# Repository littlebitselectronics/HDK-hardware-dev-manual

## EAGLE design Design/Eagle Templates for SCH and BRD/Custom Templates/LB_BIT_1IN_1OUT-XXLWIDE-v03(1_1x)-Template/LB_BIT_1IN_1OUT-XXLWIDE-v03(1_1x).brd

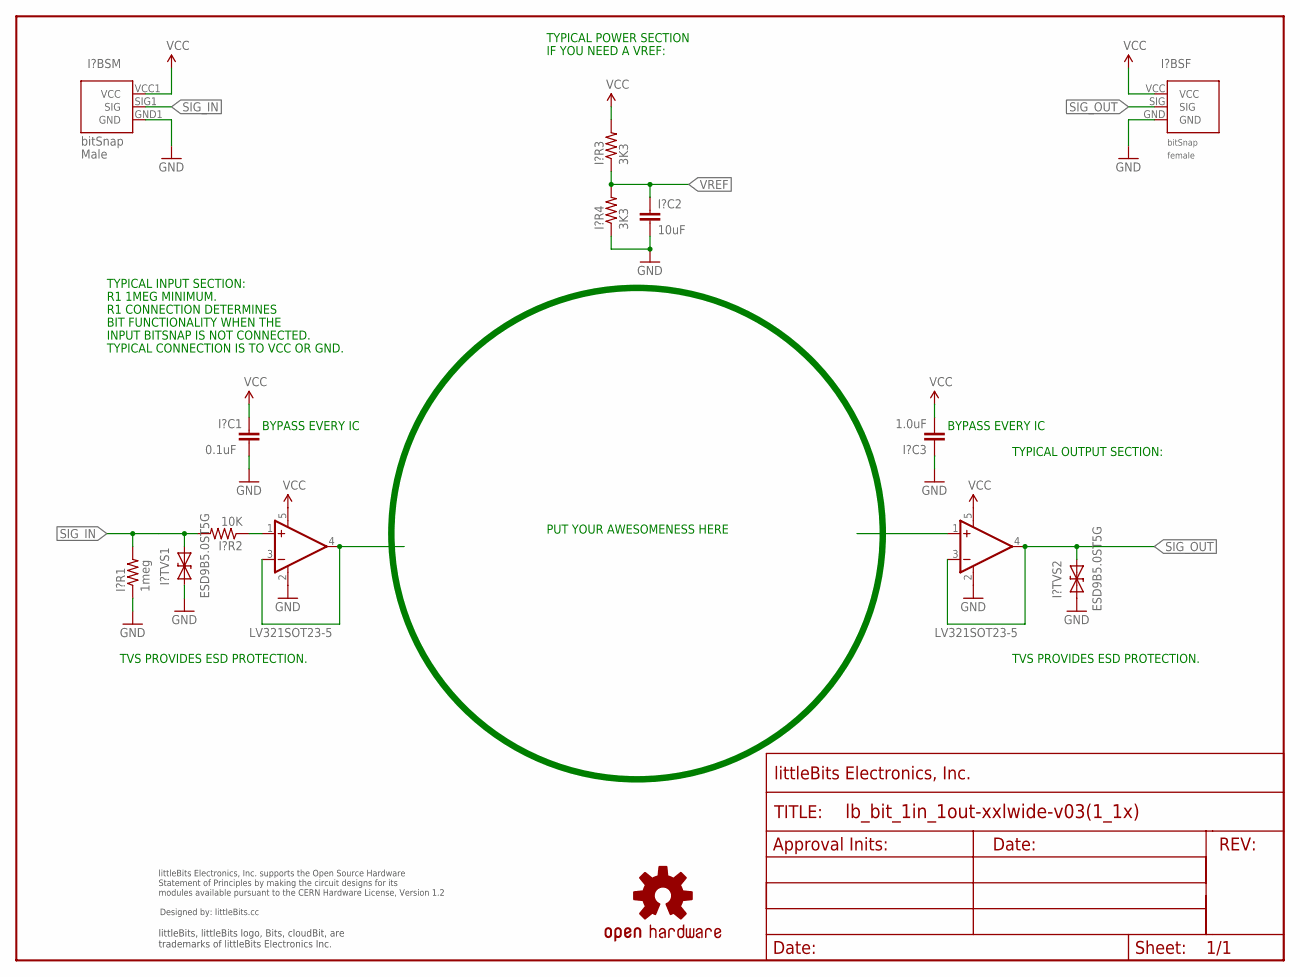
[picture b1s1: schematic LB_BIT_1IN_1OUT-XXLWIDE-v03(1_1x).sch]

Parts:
FRAME1: FRAME-LETTER; FABDWG01-OHW
I?BSF: BITSNAP_V03_FEMALE
I?BSM: BITSNAP_V03_MALE
I?C1: 0.1uF; CAP-0603
I?C2: 10uF; CAP-0603
I?C3: 1.0uF; CAP-0603
I?R1: 1meg; RES-0603
I?R2: 10K; RES-0603
I?R3, I?R4: 3K3; RES-0603
I?TVS1, I?TVS2: ESD9B5.0ST5G; SOD-923
U1, U2: LV321SOT23-5; SOT23-5
U$1: OSHWCREDIT
U$2: OSHW-LOGOL; OSHW-LOGO-L

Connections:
GND: I?BSF.GND, I?BSM.GND1 (GND), I?C1.2, I?C2.2, I?C3.1, I?R1.1, I?R4.1, I?TVS1.1 (A), I?TVS2.1 (A), U1.2 (V-), U2.2 (V-)
unnamed: U1.3 (-IN), U1.4 (OUT)
unnamed: I?R2.1, U1.1 (+IN)
SIG_IN: I?BSM.SIG1 (SIG), I?R1.2, I?R2.2, I?TVS1.2 (C)
SIG_OUT: I?BSF.SIG, I?TVS2.2 (C), U2.3 (-IN), U2.4 (OUT)
VCC: I?BSF.VCC, I?BSM.VCC1 (VCC), I?C1.1, I?C3.2, I?R3.2, U1.5 (V+), U2.5 (V+)
VREF: I?C2.1, I?R3.1, I?R4.2

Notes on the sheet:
R1 1MEG MINIMUM.
R1 CONNECTION DETERMINES
BIT FUNCTIONALITY WHEN THE
INPUT BITSNAP IS NOT CONNECTED.
TYPICAL CONNECTION IS TO VCC OR GND.
TVS PROVIDES ESD PROTECTION.
TYPICAL INPUT SECTION:
TYPICAL OUTPUT SECTION:
PUT YOUR AWESOMENESS HERE
BYPASS EVERY IC
TYPICAL POWER SECTION
IF YOU NEED A VREF:

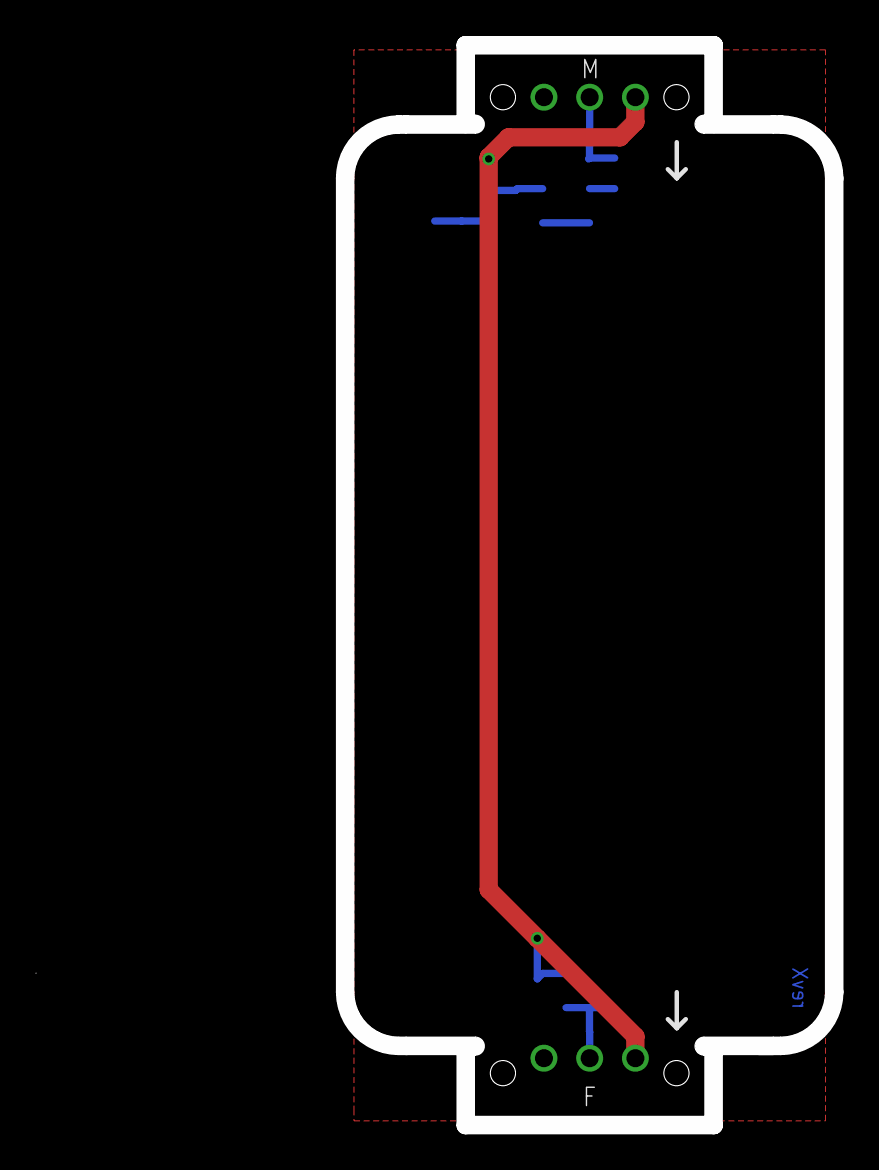
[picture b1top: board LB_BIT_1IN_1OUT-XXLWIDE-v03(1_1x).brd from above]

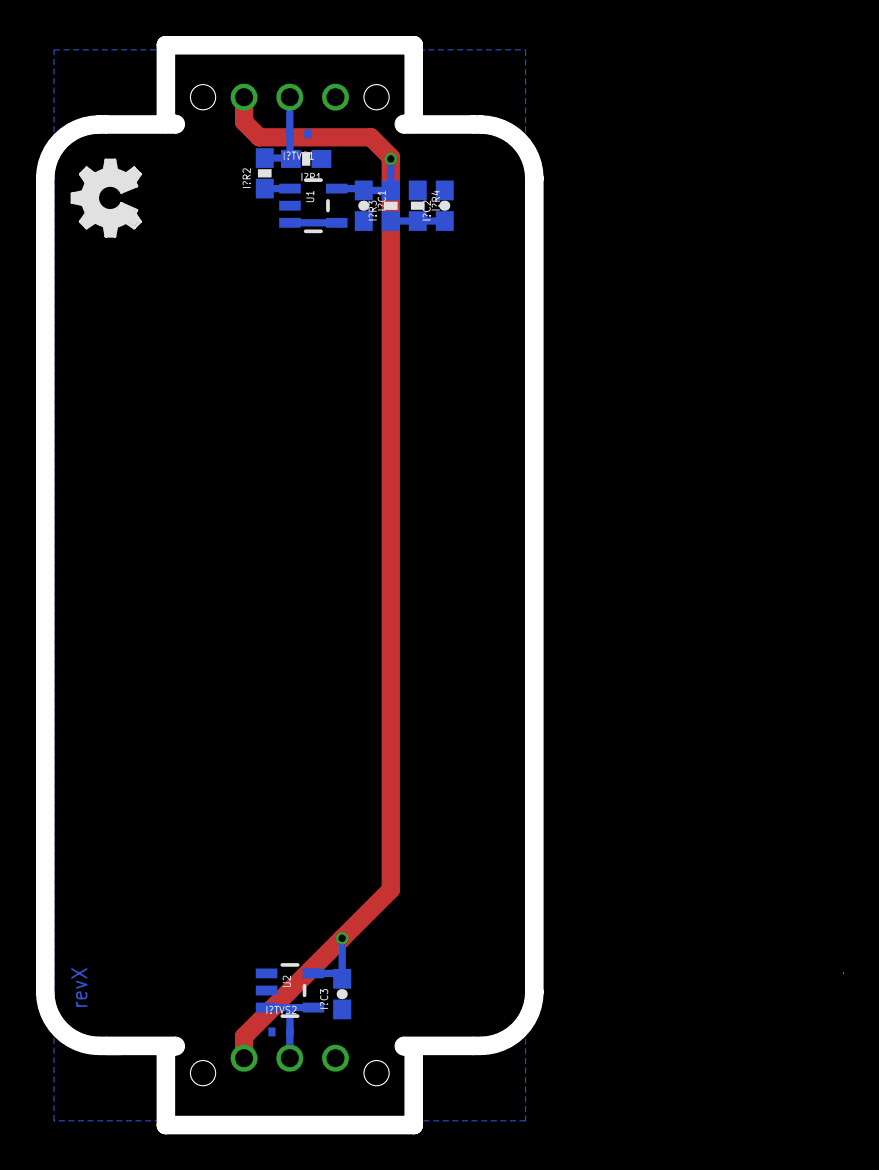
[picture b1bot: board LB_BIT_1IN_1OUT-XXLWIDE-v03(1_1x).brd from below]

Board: 2 copper layers, 26.2 x 59.0 mm, 17 parts (12 on the bottom side), 7 nets.

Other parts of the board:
U$4: OSHW_FILLX150_NOTEXT

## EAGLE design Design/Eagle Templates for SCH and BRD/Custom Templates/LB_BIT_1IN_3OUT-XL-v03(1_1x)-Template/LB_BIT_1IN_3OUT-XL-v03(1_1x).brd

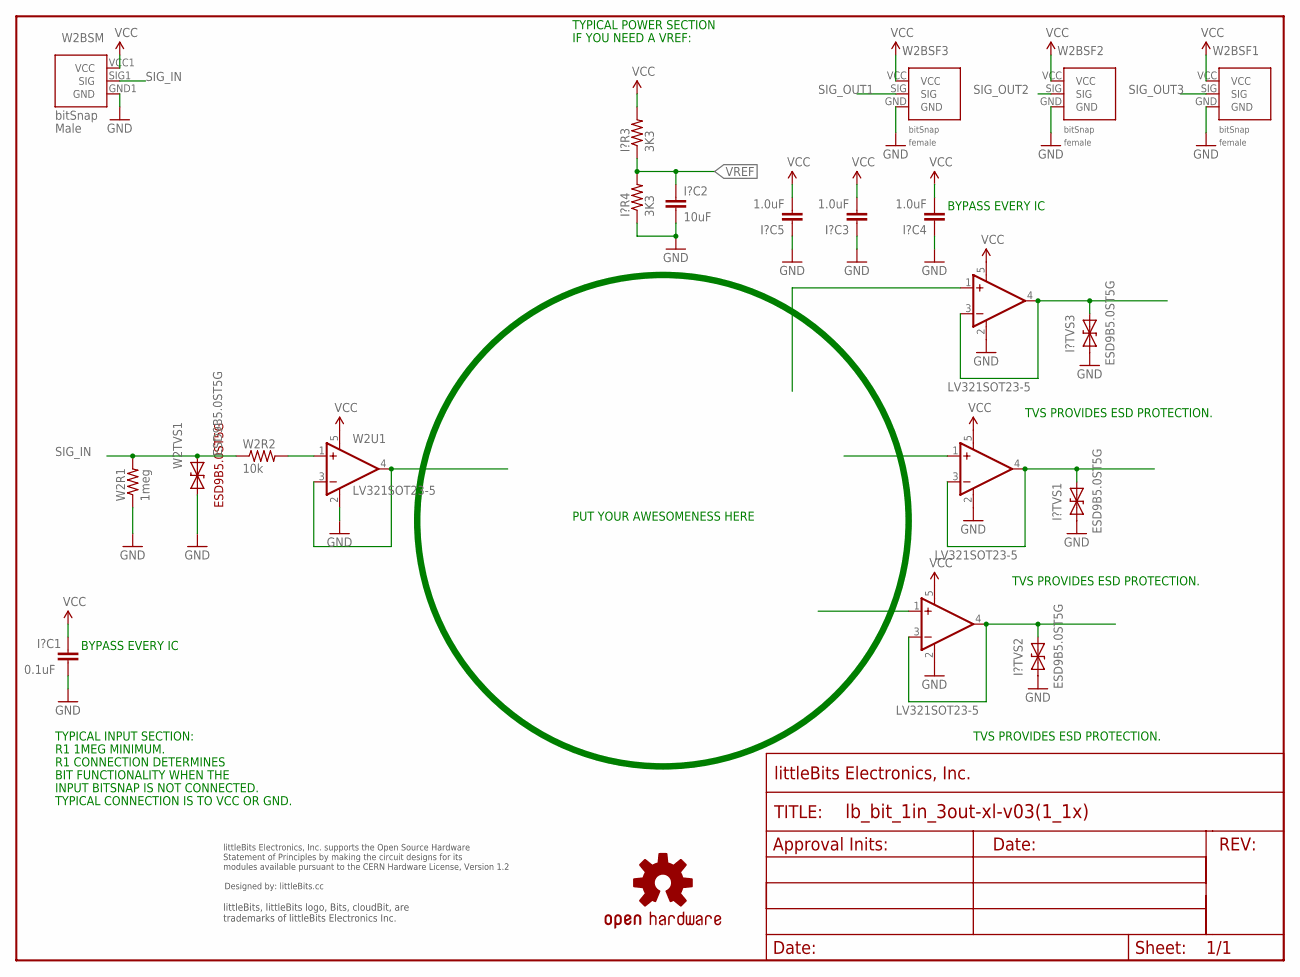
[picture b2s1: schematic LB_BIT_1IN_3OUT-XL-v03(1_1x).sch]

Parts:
FRAME1: FRAME-LETTER; FABDWG01-OHW
I?C1: 0.1uF; CAP-0603
I?C2: 10uF; CAP-0603
I?C3, I?C4, I?C5: 1.0uF; CAP-0603
I?R3, I?R4: 3K3; RES-0603
I?TVS1, I?TVS2, I?TVS3: ESD9B5.0ST5G; SOD-923
U1, U2, U3: LV321SOT23-5; SOT23-5
U$1: OSHWCREDIT
U$6: OSHW-LOGOL; OSHW-LOGO-L
W2BSF1, W2BSF2, W2BSF3: BITSNAP_V03_FEMALE
W2BSM: BITSNAP_V03_MALE
W2R1: 1meg; RES-0603
W2R2: 10k; RES-0603
W2TVS1: ESD9B5.0ST5G; SOD-923
W2U1: LV321SOT23-5; SOT23-5

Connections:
GND: I?C1.2, I?C2.2, I?C3.1, I?C4.1, I?C5.1, I?R4.1, I?TVS1.1 (A), I?TVS2.1 (A), I?TVS3.1 (A), U1.2 (V-), U2.2 (V-), U3.2 (V-), W2BSF1.GND, W2BSF2.GND, W2BSF3.GND, W2BSM.GND1 (GND), W2R1.1, W2TVS1.1 (A), W2U1.2 (V-)
unnamed: W2U1.3 (-IN), W2U1.4 (OUT)
unnamed: W2R2.2, W2U1.1 (+IN)
SIG_IN: W2BSM.SIG1 (SIG), W2R1.2, W2R2.1, W2TVS1.2 (C)
SIG_OUT1: I?TVS3.2 (C), U3.3 (-IN), U3.4 (OUT), W2BSF3.SIG
SIG_OUT2: I?TVS1.2 (C), U1.3 (-IN), U1.4 (OUT), W2BSF2.SIG
SIG_OUT3: I?TVS2.2 (C), U2.3 (-IN), U2.4 (OUT), W2BSF1.SIG
VCC: I?C1.1, I?C3.2, I?C4.2, I?C5.2, I?R3.2, U1.5 (V+), U2.5 (V+), U3.5 (V+), W2BSF1.VCC, W2BSF2.VCC, W2BSF3.VCC, W2BSM.VCC1 (VCC), W2U1.5 (V+)
VREF: I?C2.1, I?R3.1, I?R4.2

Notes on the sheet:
R1 1MEG MINIMUM.
R1 CONNECTION DETERMINES
BIT FUNCTIONALITY WHEN THE
INPUT BITSNAP IS NOT CONNECTED.
TYPICAL CONNECTION IS TO VCC OR GND.
TYPICAL INPUT SECTION:
TYPICAL POWER SECTION
IF YOU NEED A VREF:
TVS PROVIDES ESD PROTECTION.
PUT YOUR AWESOMENESS HERE
BYPASS EVERY IC

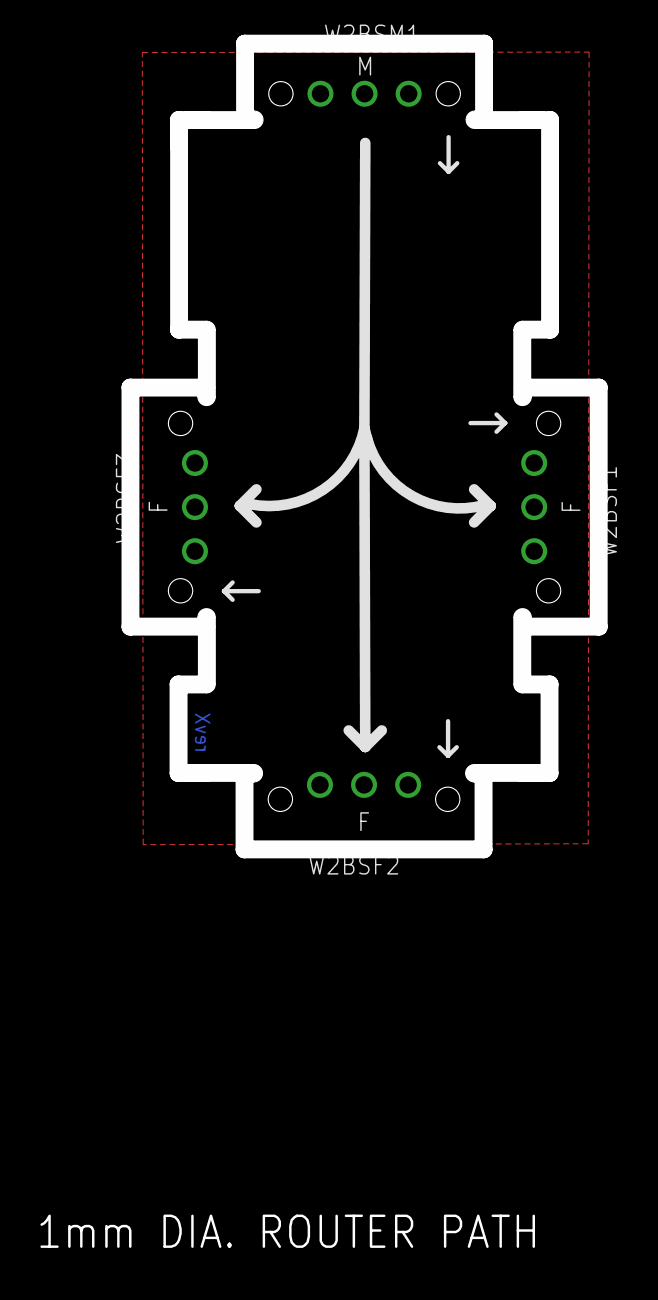
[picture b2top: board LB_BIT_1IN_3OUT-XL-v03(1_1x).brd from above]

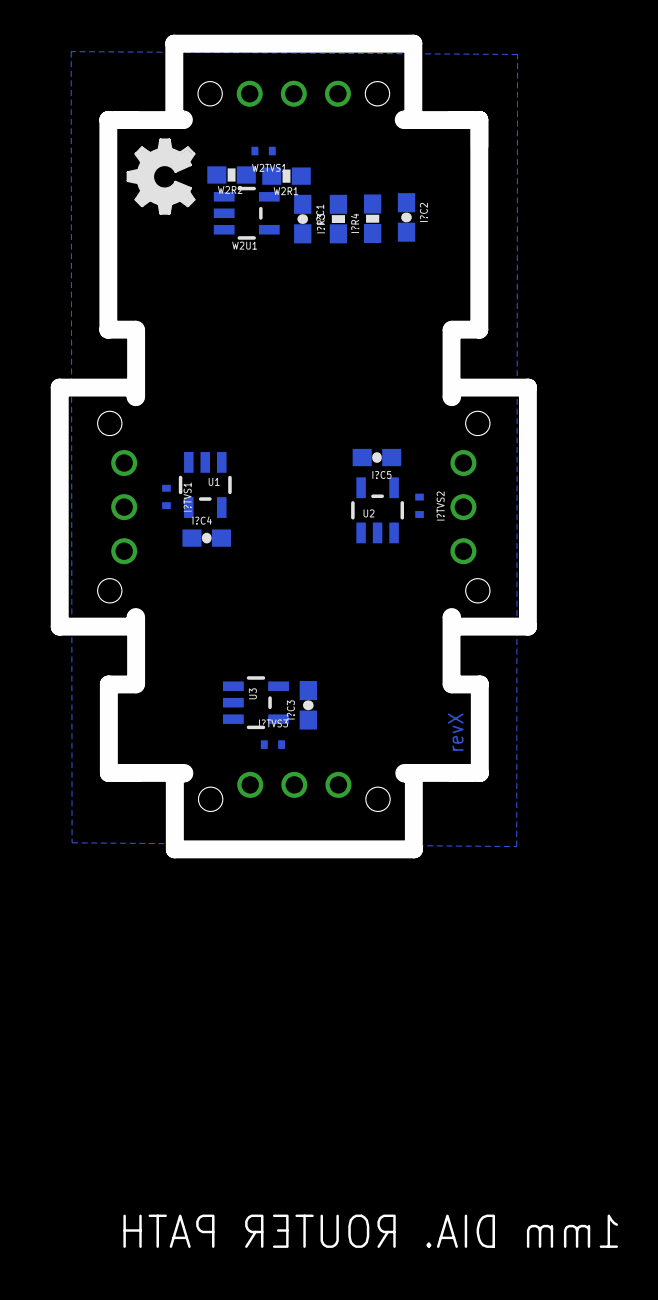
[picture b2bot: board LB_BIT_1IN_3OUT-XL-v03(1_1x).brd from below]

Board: 2 copper layers, 26.0 x 45.4 mm, 25 parts (17 on the bottom side), 9 nets.

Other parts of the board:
U$5: OSHW_FILLX150_NOTEXT

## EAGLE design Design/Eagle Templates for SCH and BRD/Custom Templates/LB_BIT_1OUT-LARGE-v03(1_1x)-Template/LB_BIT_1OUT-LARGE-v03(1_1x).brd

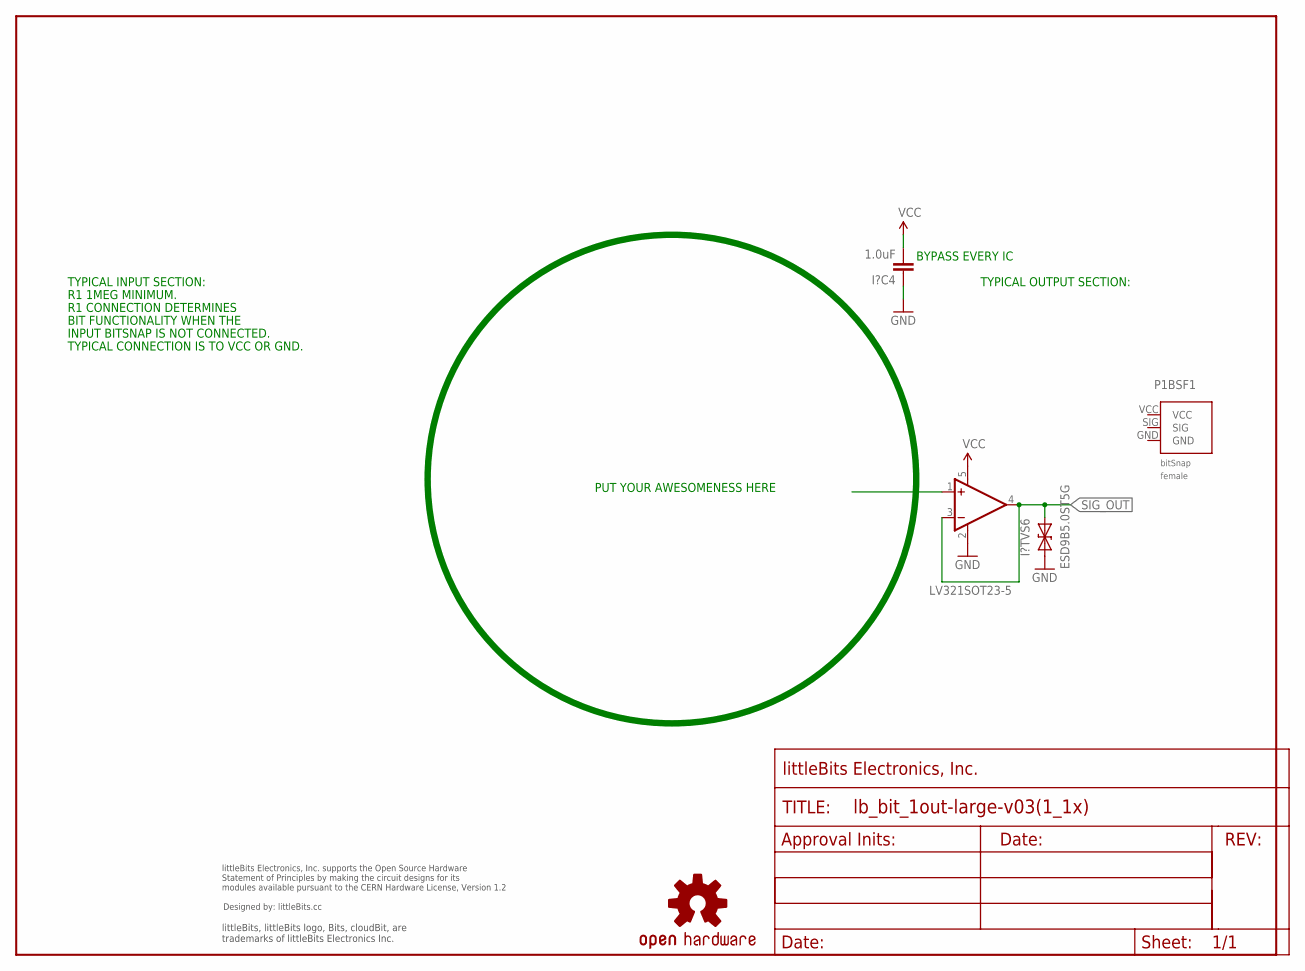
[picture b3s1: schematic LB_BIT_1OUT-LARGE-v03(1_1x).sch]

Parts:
FRAME1: FRAME-LETTER; FABDWG01-OHW
I?C4: 1.0uF; CAP-0603
I?TVS6: ESD9B5.0ST5G; SOD-923
P1BSF1: BITSNAP_V03_FEMALE
U6: LV321SOT23-5; SOT23-5
U$3: OSHW-LOGOL; OSHW-LOGO-L
U$4: OSHWCREDIT

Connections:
GND: I?C4.1, I?TVS6.1 (A), U6.2 (V-)
SIG_OUT: I?TVS6.2 (C), U6.3 (-IN), U6.4 (OUT)
VCC: I?C4.2, U6.5 (V+)

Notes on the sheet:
R1 1MEG MINIMUM.
R1 CONNECTION DETERMINES
BIT FUNCTIONALITY WHEN THE
INPUT BITSNAP IS NOT CONNECTED.
TYPICAL CONNECTION IS TO VCC OR GND.
TYPICAL INPUT SECTION:
PUT YOUR AWESOMENESS HERE
TYPICAL OUTPUT SECTION:
BYPASS EVERY IC

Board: 2 copper layers, 9 parts (3 on the bottom side), 3 nets, no tracks yet.

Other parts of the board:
U$2: OSHW_FILLX150_NOTEXT
U$12: LB_PWR_LEGS

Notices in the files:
parts and their libraries:
LITTLEBITS: modules available pursuant to the CERN Hardware License,
Version 1.2
LITTLEBITS: modules available pursuant to the CERN Hardware License, Version 1.2
SparkFun_NEW: Licensing: CC v3.0 Share-Alike You are welcome to use this library for commercial purposes.
